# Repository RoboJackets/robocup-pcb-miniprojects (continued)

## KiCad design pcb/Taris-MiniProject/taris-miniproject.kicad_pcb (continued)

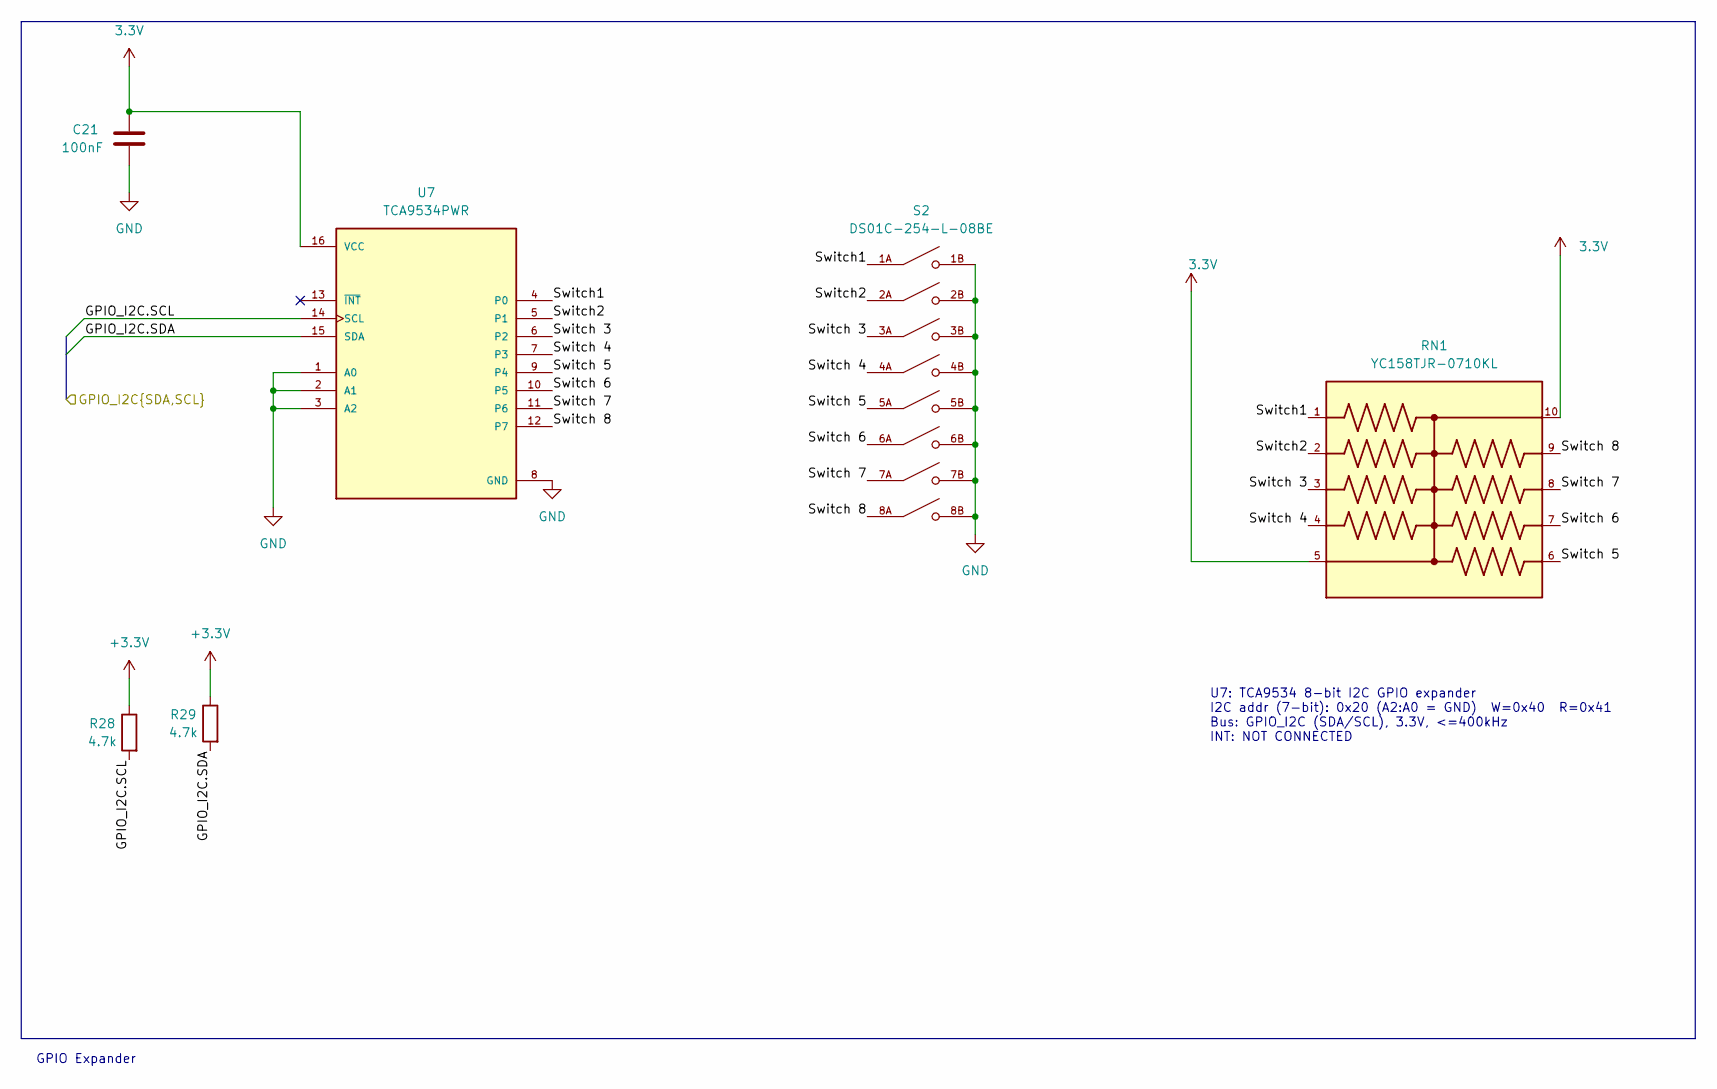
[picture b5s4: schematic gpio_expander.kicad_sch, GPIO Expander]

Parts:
C21: 100nF; C_0603_1608Metric; Manufacturer P/N CC0603KRX5R8BB104
R28, R29: 4.7k; R_0402_1005Metric; Manufacturer P/N RC0402FR-134K7L
RN1: YC158TJR-0710KL; RESCAXE64P320X160X70-10N; Manufacturer P/N YC158TJR-0710KL
S2: DS01C-254-L-08BE; SW_DS01C-254-L-08BE; PARTREV 1.0
U7: TCA9534PWR; SOP65P640X120-16N; PARTREV D

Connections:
3.3V: C21.1, RN1.5, RN1.10, U7.16 (VCC); also elsewhere on the board
+3.3V: R28.1, R29.1; also elsewhere on the board
/GPIO Expander/Switch1: RN1.1, S2.1A, U7.4 (P0)
/GPIO Expander/Switch2: RN1.2, S2.2A, U7.5 (P1)
/GPIO Expander/Switch 3: RN1.3, S2.3A, U7.6 (P2)
/GPIO Expander/Switch 4: RN1.4, S2.4A, U7.7 (P3)
/GPIO Expander/Switch 5: RN1.6, S2.5A, U7.9 (P4)
/GPIO Expander/Switch 6: RN1.7, S2.6A, U7.10 (P5)
/GPIO Expander/Switch 7: RN1.8, S2.7A, U7.11 (P6)
/GPIO Expander/Switch 8: RN1.9, S2.8A, U7.12 (P7)
/GPIO_I2C.SCL: R28.2, U7.14 (SCL); also elsewhere on the board
/GPIO_I2C.SDA: R29.2, U7.15 (SDA); also elsewhere on the board
GND: C21.2, S2.1B, S2.2B, S2.3B, S2.4B, S2.5B, S2.6B, S2.7B, S2.8B, U7.1 (A0), U7.2 (A1), U7.3 (A2), U7.8 (GND); also elsewhere on the board

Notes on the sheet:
U7: TCA9534 8-bit I2C GPIO expander I2C addr (7-bit): 0x20 (A2:A0 = GND) W=0x40 R=0x41 Bus: GPIO_I2C (SDA/SCL), 3.3V, <=400kHz INT: NOT CONNECTED
GPIO Expander

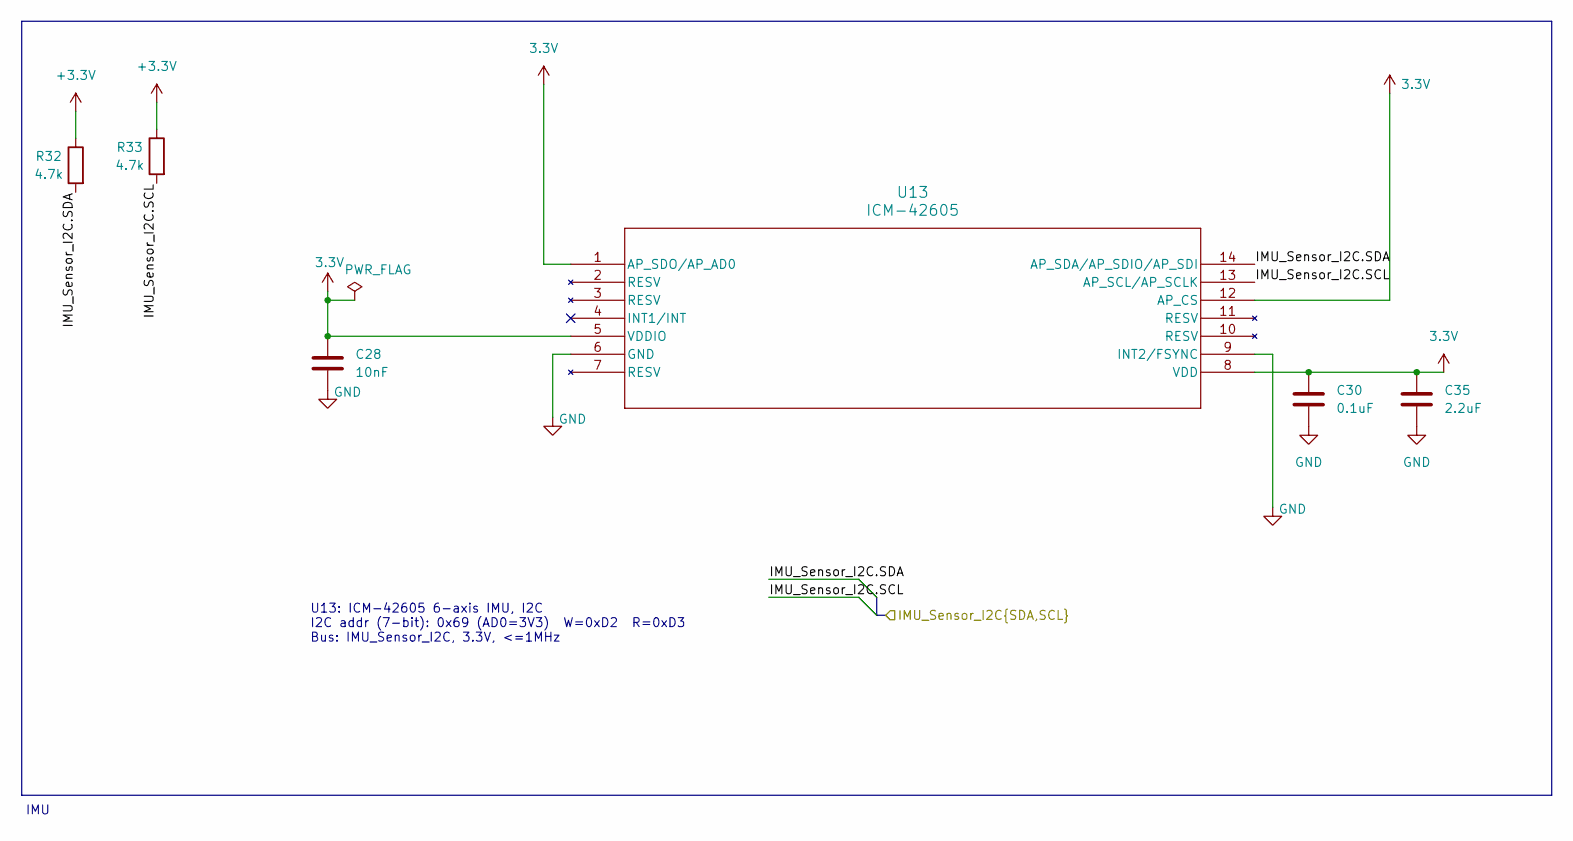
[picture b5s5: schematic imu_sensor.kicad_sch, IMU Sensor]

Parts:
C28: 10nF; C_0603_1608Metric; Manufacturer P/N GMC10X7R103K50NT
C30: 0.1uF; C_0603_1608Metric; Manufacturer P/N CC0603KRX5R8BB104
C35: 2.2uF; C_0603_1608Metric; Manufacturer P/N GMC10X7R225K25NT
R32, R33: 4.7k; R_0402_1005Metric; Manufacturer P/N RC0402FR-134K7L
U13: ICM-42605; LGA14_2P5X3X0P91_IVS; Manufacturer P/N ICM-42605

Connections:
3.3V: C28.1, C30.1, C35.1, U13.1 (AP_SDO/AP_AD0), U13.5 (VDDIO), U13.8 (VDD), U13.12 (AP_CS); also elsewhere on the board
+3.3V: R32.1, R33.1; also elsewhere on the board
/IMU_Sensor_I2C.SCL: R33.2, U13.13 (AP_SCL/AP_SCLK); also elsewhere on the board
/IMU_Sensor_I2C.SDA: R32.2, U13.14 (AP_SDA/AP_SDIO/AP_SDI); also elsewhere on the board
GND: C28.2, C30.2, C35.2, U13.6 (GND), U13.9 (INT2/FSYNC); also elsewhere on the board

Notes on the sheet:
IMU
U13: ICM-42605 6-axis IMU, I2C I2C addr (7-bit): 0x69 (AD0=3V3) W=0xD2 R=0xD3 Bus: IMU_Sensor_I2C, 3.3V, <=1MHz

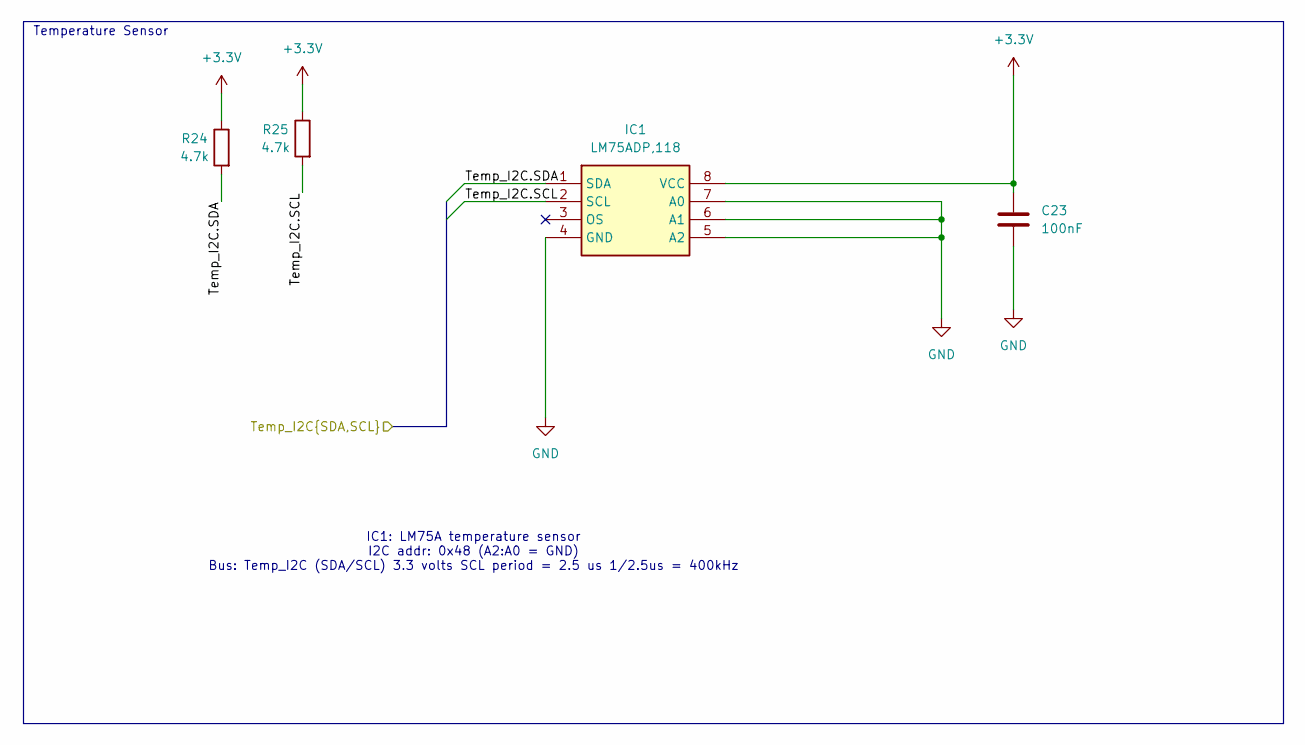
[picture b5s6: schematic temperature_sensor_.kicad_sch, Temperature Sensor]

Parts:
C23: 100nF; C_0603_1608Metric; Manufacturer P/N CC0603KRX5R8BB104
IC1: LM75ADP,118; SOP65P490X110-8N; Manufacturer_Part_Number LM75ADP,118; Mouser Part Number 771-LM75ADP-T
R24, R25: 4.7k; R_0402_1005Metric; Manufacturer P/N RC0402FR-134K7L

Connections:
+3.3V: C23.1, IC1.8 (VCC), R24.1, R25.1; also elsewhere on the board
/Temp_I2C.SCL: IC1.2 (SCL), R25.2; also elsewhere on the board
/Temp_I2C.SDA: IC1.1 (SDA), R24.2; also elsewhere on the board
GND: C23.2, IC1.4 (GND), IC1.5 (A2), IC1.6 (A1), IC1.7 (A0); also elsewhere on the board

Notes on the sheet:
IC1: LM75A temperature sensor I2C addr: 0x48 (A2:A0 = GND) Bus: Temp_I2C (SDA/SCL) 3.3 volts SCL period = 2.5 us 1/2.5us = 400kHz
Temperature Sensor

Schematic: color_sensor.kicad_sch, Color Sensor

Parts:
C27: 100nF; C_0603_1608Metric; Manufacturer P/N CC0603KRX5R8BB104
R30, R31: 4.7k; R_0402_1005Metric; Manufacturer P/N RC0402FR-134K7L
U12: VEML3328; Manufacturer P/N VEML3328

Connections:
3.3V: C27.1, U12.4 (VDD); also elsewhere on the board
+3.3V: R30.1, R31.1; also elsewhere on the board
/Color_I2C.SCL: R31.2, U12.3 (SCL); also elsewhere on the board
/Color_I2C.SDA: R30.2, U12.2 (SDA); also elsewhere on the board
GND: C27.2, U12.1 (GND); also elsewhere on the board

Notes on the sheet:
Color Sensor
U12: VEML3328 RGB/IR color sensor, I2C I2C addr (7-bit): 0x10 W=0x20 R=0x21 Bus: Color_I2C (SDA/SCL), 3.3V, <=400kHz

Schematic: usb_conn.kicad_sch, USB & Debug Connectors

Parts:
C17, C18, C24: 1u; C_0402_1005Metric; Manufacturer P/N GRM155Z71A105KE01J
J2: SWD; PinHeader_1x04_P2.54mm_Vertical; Manufacturer P/N 61300411121
J5: USB_B_Micro; USB_Micro-B_Amphenol_10118194-0001LF_Horizontal; Manufacturer P/N 10118194-0001LF
R13: 10K; R_0402_1005Metric; Manufacturer P/N RC0402FR-0710KL
U3: AP2112K-3.3; SOT-23-5; Manufacturer P/N AP2112K-3.3TRG1
U4, U5: USBLC6-2P6; SOT-666; Manufacturer P/N USBLC6-2SC6
U8, U9: LM66100DCK; SOT-363_SC-70-6; Manufacturer P/N LM66100DCKR

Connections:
+3.3V: C18.2, J2.1, U3.5 (VOUT), U5.5 (VBUS); also elsewhere on the board
/SLAVE_POWER: C17.2, C24.2, U3.1 (VIN), U3.3 (EN), U8.6 (VOUT), U9.6 (VOUT); also elsewhere on the board
/SPI_MASTER_INPUT: U8.3 (~CE), U9.1 (VIN); also elsewhere on the board
/SWD.CLK: U5.6 (I/O1); also elsewhere on the board
/SWD.DIO: U5.4 (I/O2); also elsewhere on the board
/USB.DM: U4.6 (I/O1); also elsewhere on the board
/USB.DP: U4.4 (I/O2); also elsewhere on the board
GND: C17.1, C18.1, C24.1, J2.4, J5.5 (GND), U3.2 (GND), U4.2 (GND), U5.2 (GND), U8.2 (GND), U9.2 (GND); also elsewhere on the board
unnamed: J2.2, U5.1 (I/O1)
unnamed: J2.3, U5.3 (I/O2)
unnamed: J5.3 (D+), U4.3 (I/O2)
unnamed: J5.2 (D-), U4.1 (I/O1)
unnamed: R13.1, U8.5 (ST), U9.3 (~CE)
VBUS: J5.1 (VBUS), R13.2, U4.5 (VBUS), U8.1 (VIN); also elsewhere on the board

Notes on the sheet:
SWD Debug Connector
Pull down resistor removed to avoid shorting the output. Capacitor kept so switching doesn't affect smoothness
Micro USB
MUX for SPI and Micro USB
3.3 V 600 mA LDO
0.5 mA of current when pulled low

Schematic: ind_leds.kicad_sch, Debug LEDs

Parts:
D3, D4, D5: RED; LED_0603_1608Metric; Manufacturer P/N LTST-C190KRKT
R15, R16, R17: 1k; R_0402_1005Metric; Manufacturer P/N RC0402FR-071KL

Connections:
3.3V: R17.2; also elsewhere on the board
/SLAVE_POWER: R16.2; also elsewhere on the board
GND: D3.1 (K), D4.1 (K), D5.1 (K); also elsewhere on the board
unnamed: D3.2 (A), R15.1
unnamed: D4.2 (A), R16.1
unnamed: D5.2 (A), R17.1
VBUS: R15.2; also elsewhere on the board

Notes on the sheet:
USB: 5 volts / 1 kOhm = 3.0 mA SPI_SLAVE_LED: 5 volts / 1 kOhm = 3.0 mA Color_Sensor_Power: 3.3 volts / 1 kOhm = 1.3 mA
Indicator LEDs

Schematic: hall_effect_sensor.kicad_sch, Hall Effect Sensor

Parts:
C22: 100nF; C_0603_1608Metric; Manufacturer P/N CC0603KRX5R8BB104
R26, R27: 4.7k; R_0402_1005Metric; Manufacturer P/N RC0402FR-134K7L
U11: TMAG5273C1QDBVR; SOT95P280X140-6N; PARTREV B

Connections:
3.3V: C22.1; also elsewhere on the board
+3.3V: R26.1, R27.1; also elsewhere on the board
/Hall_I2C.SCL: R26.2, U11.1 (SCL); also elsewhere on the board
/Hall_I2C.SDA: R27.2, U11.6 (SDA); also elsewhere on the board
GND: C22.2, U11.2 (GND), U11.3 (TEST), U11.4 (VCC); also elsewhere on the board

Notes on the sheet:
Hall Effect Sensor
U11: TMAG5273C1 3-axis Hall sensor, I2C I2C addr (7-bit): 0x78 (C1 default, VERIFY on HW) Bus: Hall_I2C (SDA/SCL), 3.3V, <=400kHz INT: NOT CONNECTED, set MASK_INTB=1 in firmware TEST: tied to GND (required)

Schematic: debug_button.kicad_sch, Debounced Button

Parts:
C15: 100nF; C_0402_1005Metric; Manufacturer P/N CC0603KRX5R8BB104
R7, R8: 10k; R_0402_1005Metric; Manufacturer P/N RC0402FR-0710KL
SW3: PTS810; SW_SPST_PTS810; Manufacturer P/N PTS810SJK250SMTR LFS

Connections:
+3.3V: SW3.1 (A); also elsewhere on the board
/MCU/gp_btn_a: C15.1, R8.2; also elsewhere on the board
GND: C15.2, R7.2; also elsewhere on the board
unnamed: R7.1, R8.1, SW3.2 (B)

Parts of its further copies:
C16: 100nF; C_0402_1005Metric; Manufacturer P/N CC0603KRX5R8BB104
R9, R10: 10k; R_0402_1005Metric; Manufacturer P/N RC0402FR-0710KL
SW4: PTS810; SW_SPST_PTS810; Manufacturer P/N PTS810SJK250SMTR LFS

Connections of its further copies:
+3.3V: SW4.1 (A); also elsewhere on the board
/MCU/gp_btn_b: C16.1, R10.2; also elsewhere on the board
GND: C16.2, R9.2; also elsewhere on the board
unnamed: R9.1, R10.1, SW4.2 (B)

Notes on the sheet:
RC low-pass filter -3 dB cutoff: 159.15 Hz

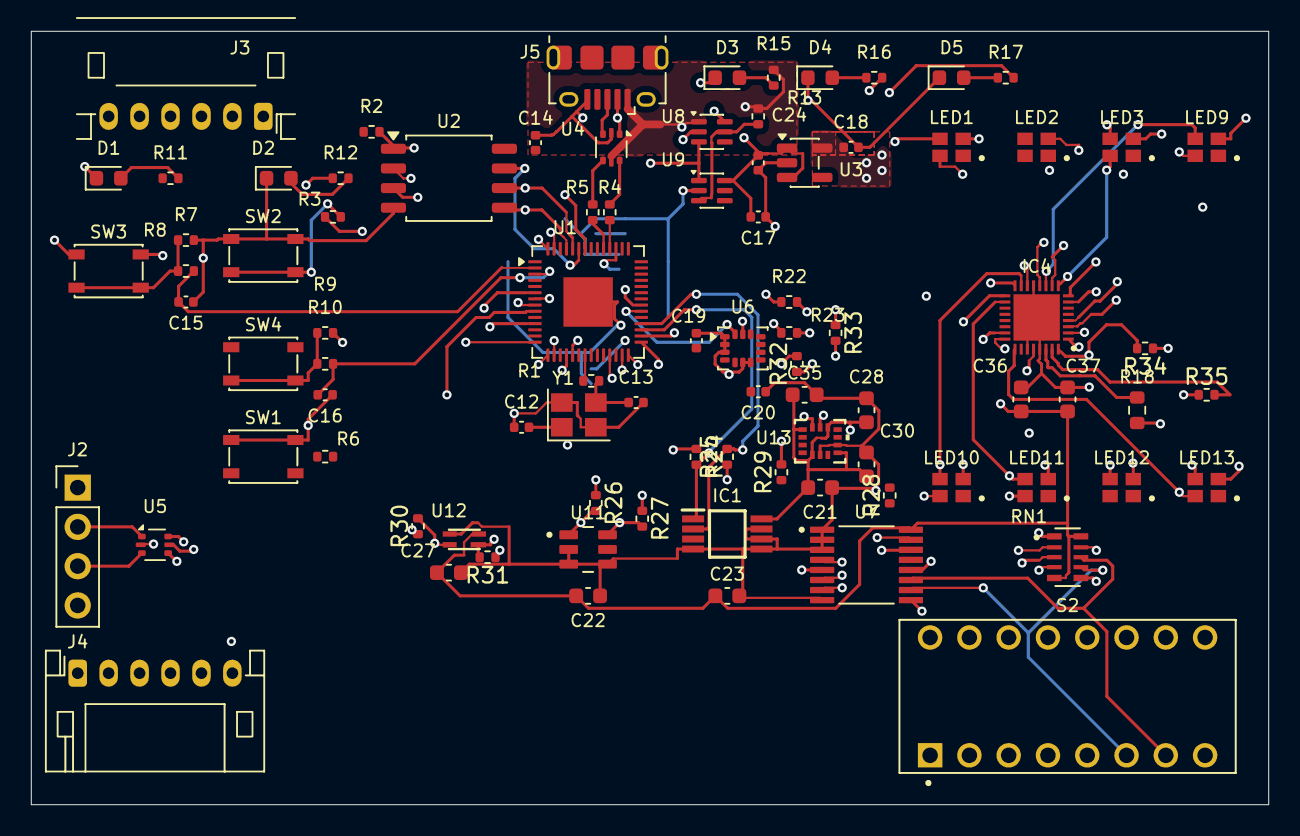
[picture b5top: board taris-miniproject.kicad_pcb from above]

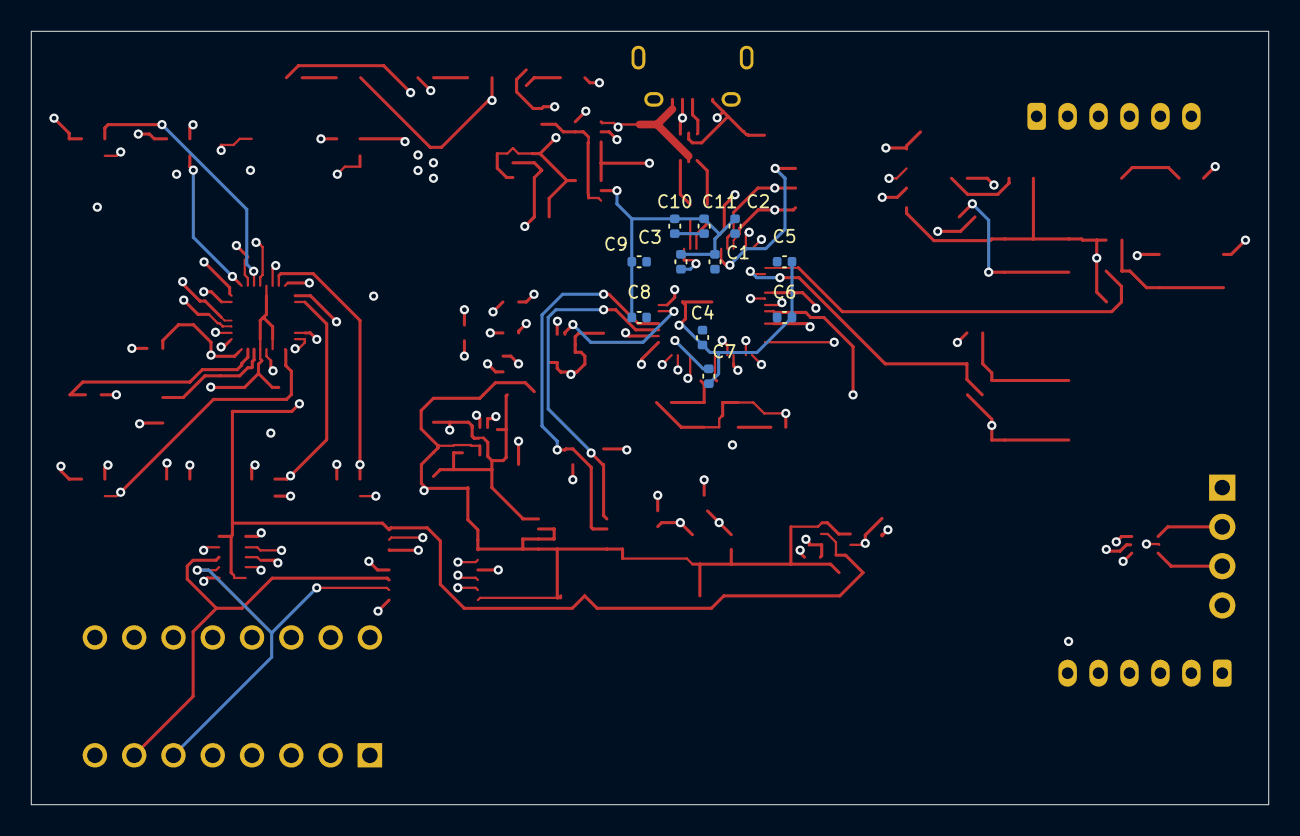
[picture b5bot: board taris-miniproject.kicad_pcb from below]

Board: 4 copper layers, 80.0 x 50.0 mm, 99 parts (11 on the bottom side), 95 nets.

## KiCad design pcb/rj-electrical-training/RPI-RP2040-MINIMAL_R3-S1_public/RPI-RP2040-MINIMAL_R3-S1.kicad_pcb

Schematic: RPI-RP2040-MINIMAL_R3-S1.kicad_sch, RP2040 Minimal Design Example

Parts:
C1, C4, C17: 10u; generic_capc2012x125; voltage 16V; tolerance 10%; part_uid RP-01GYSK-AVBE41
C2, C3: 15p; generic_capc1005x50; voltage 50V; tolerance 5%; part_uid RP-01C89W-LLY9XV
C5, C6, C7, C9, C11, C12, C13, C14, C15, C16: 100n; generic_capc1005x50; voltage 25V; tolerance 10%; part_uid RP-01BJ9Y-KRGF41
C8, C10: 1u; generic_capc1005x50; voltage 16V; tolerance 10%; part_uid RP-01GYSK-L7FEKV
J1: 10103594-0001LF; amphenol_10103594-0001lf; part_uid RP-019A1P-1JAX7V
J2: TSW-102-07-G-S; samtec_tsw-102-07-g-s; part_uid RP-01JV5X-LY21H5
J3, J4: TSW-118-07-L-D; samtec_tsw-118-07-l-d; part_uid RP-01JWH2-G371Y4
MH1, MH2, MH3, MH4: NPTH FD2.75mm SM3.15mm KO6mm; none_mh_npth_fd2p75mm_sm3p15mm_ko6mm; part_uid RP-01HF5R-LCTEJS
PCB1: R3; manufacturer_pn XXX
R1, R5: 1k; generic_resc1005x35; tolerance 1%; voltage 50V; part_uid RP-019A1P-4Z6ZWY
R2: 10k; generic_resc1005x35; tolerance 1%; voltage 50V; part_uid RP-019A1P-53DHSX; not fitted
R3, R4: 27; generic_resc1005x35; tolerance 1%; voltage 50V; part_uid RP-01C89V-LTEYC4
SBREV1: S1
U1: NCP1117ST33T3G; onsemi_ncp1117st33t3g; voltage 3.3V; part_uid RP-01JWD9-7JRX6J
U2: W25Q128JVSIQ; generic_soic127p790x195-8; voltage 2.7-3.6V; part_uid RP-01JWD4-F1H4N9
U3: RP2040; rpi_rp2040_vias; part_uid RP-01EKHS-ZTKTEH
VARIANT1: RPI-RP2040-MINIMAL
X1: 12MHz; generic_xtalcc320x250x80-4; tolerance 30ppm; part_uid RP-01G8X7-GS352B

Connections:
+1V1: C6.1, C7.1, C8.1, U3.23 (DVDD), U3.45 (VREG_VOUT), U3.50 (DVDD)
+3V3: C4.1, C5.1, C9.1, C10.1, C11.1, C12.1, C13.1, C14.1, C15.1, C16.1, C17.1, J3.2, R2.1, U1.2 (OUT), U1.4 (OUT), U2.8 (VCC), U3.1 (IOVDD), U3.10 (IOVDD), U3.22 (IOVDD), U3.33 (IOVDD), U3.42 (IOVDD), U3.43 (ADC_AVDD), U3.44 (VREG_IN), U3.48 (USB_VDD), U3.49 (IOVDD)
/GPIO0: J3.4, U3.2 (GPIO0)
/GPIO1: J3.6, U3.3 (GPIO1)
/GPIO2: J3.8, U3.4 (GPIO2)
/GPIO3: J3.10, U3.5 (GPIO3)
/GPIO4: J3.12, U3.6 (GPIO4)
/GPIO5: J3.14, U3.7 (GPIO5)
/GPIO6: J3.16, U3.8 (GPIO6)
/GPIO7: J3.18, U3.9 (GPIO7)
/GPIO8: J3.20, U3.11 (GPIO8)
/GPIO9: J3.22, U3.12 (GPIO9)
/GPIO10: J3.24, U3.13 (GPIO10)
/GPIO11: J3.26, U3.14 (GPIO11)
/GPIO12: J3.28, U3.15 (GPIO12)
/GPIO13: J3.30, U3.16 (GPIO13)
/GPIO14: J3.32, U3.17 (GPIO14)
/GPIO15: J3.34, U3.18 (GPIO15)
/GPIO16: J4.27, U3.27 (GPIO16)
/GPIO17: J4.25, U3.28 (GPIO17)
/GPIO18: J4.23, U3.29 (GPIO18)
/GPIO19: J4.21, U3.30 (GPIO19)
/GPIO20: J4.19, U3.31 (GPIO20)
/GPIO21: J4.17, U3.32 (GPIO21)
/GPIO22: J4.15, U3.34 (GPIO22)
/GPIO23: J4.13, U3.35 (GPIO23)
/GPIO24: J4.11, U3.36 (GPIO24)
/GPIO25: J4.9, U3.37 (GPIO25)
/GPIO26_ADC0: J4.7, U3.38 (GPIO26_ADC0)
/GPIO27_ADC1: J4.5, U3.39 (GPIO27_ADC1)
/GPIO28_ADC2: J4.3, U3.40 (GPIO28_ADC2)
/GPIO29_ADC3: J4.1, U3.41 (GPIO29_ADC3)
/QSPI_SCLK: U2.6 (CLK), U3.52 (QSPI_SCLK)
/QSPI_SD0: U2.5 (DI_IO0), U3.53 (QSPI_SD0)
/QSPI_SD1: U2.2 (DO_IO1), U3.55 (QSPI_SD1)
/QSPI_SD2: U2.3 (~WP_IO2), U3.54 (QSPI_SD2)
/QSPI_SD3: U2.7 (~HOLD_IO3), U3.51 (QSPI_SD3)
/QSPI_SS: R1.1, R2.2, U2.1 (~CS), U3.56 (QSPI_~SS)
/RUN: J4.29, U3.26 (RUN)
/SWCLK: J4.33, U3.24 (SWCLK)
/SWD: J4.31, U3.25 (SWD)
/USB_D+: J1.3 (D+), R3.1
/USB_D-: J1.2 (D-), R4.1
/XIN: C2.1, U3.20 (XIN), X1.1
/XOUT: R5.2, U3.21 (XOUT)
/~USB_BOOT: J2.1, R1.2
GND: C1.2, C2.2, C3.2, C4.2, C5.2, C6.2, C7.2, C8.2, C9.2, C10.2, C11.2, C12.2, C13.2, C14.2, C15.2, C16.2, C17.2, J1.5 (GND), J1.6 (SH), J1.7 (SH), J1.8 (SH), J1.9 (SH), J1.10 (SH), J1.11 (SH), J2.2, J3.1, J3.3, J3.5, J3.7, J3.9, J3.11, J3.13, J3.15, J3.17, J3.19, J3.21, J3.23, J3.25, J3.27, J3.29, J3.31, J3.33, J3.35, J3.36, J4.2, J4.4, J4.6, J4.8, J4.10, J4.12, J4.14, J4.16, J4.18, J4.20, J4.22, J4.24, J4.26, J4.28, J4.30, J4.32, J4.34, J4.35, J4.36, U1.1 (GND), U2.4 (GND), U3.19 (TESTEN), U3.57 (GND), X1.2, X1.4
unnamed: C3.1, R5.1, X1.3
unnamed: R4.2, U3.46 (USB_DM)
unnamed: R3.2, U3.47 (USB_DP)
VBUS: C1.1, J1.1 (VCC), U1.3 (IN)

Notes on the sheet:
IOs
Power
Crystal
Make sure C8 is close to pin 45 of RP2040
Make sure C10 is close to pin 44 of RP2040
Note: S1 schematic revision indicates that this is the 1st revision of the schematic/BOM associated with the R3 PCB. R3-S1 therefore uniquely identifies the fully built PCB Assembly (PCBA). This is a change from the previous revision numbering to align with the internal Raspberry Pi product revisio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
Make sure R3 and R4 are close to RP2040
Flash

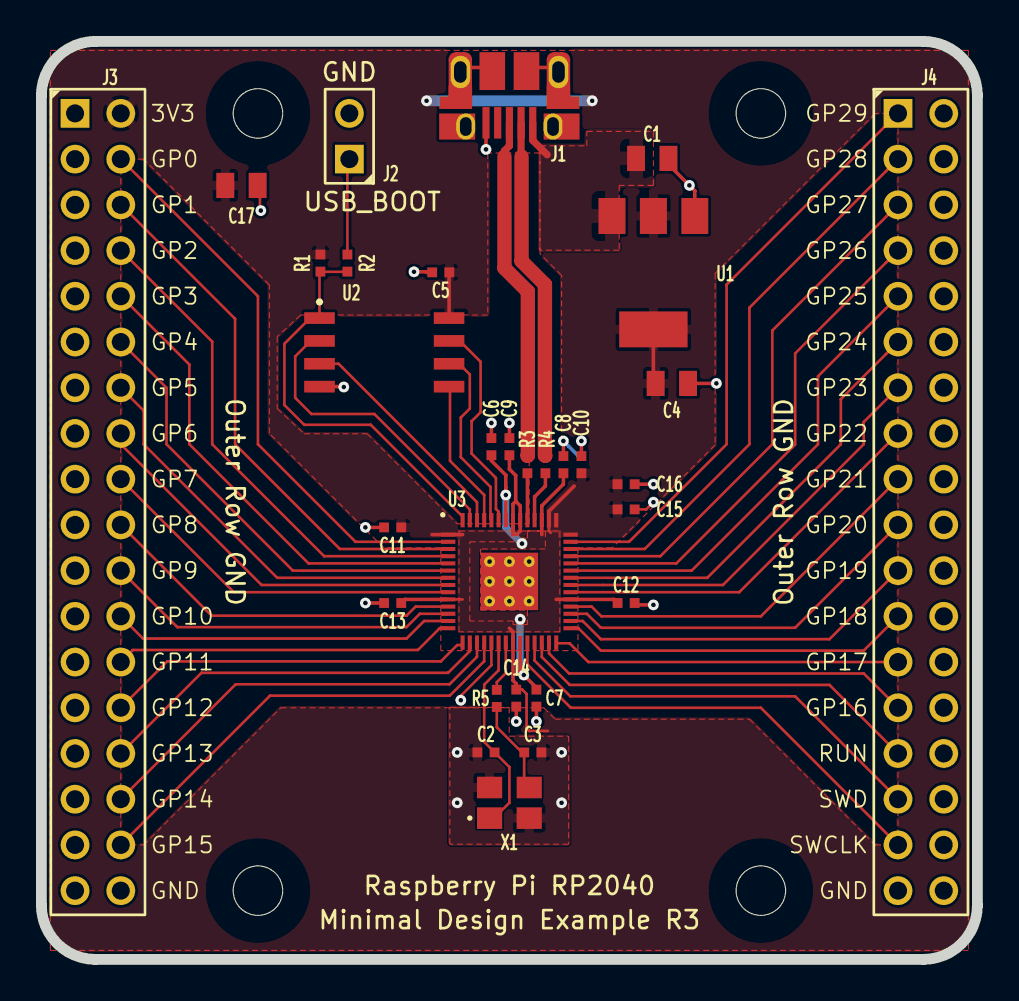
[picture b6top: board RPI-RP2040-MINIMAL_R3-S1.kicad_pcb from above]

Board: 2 copper layers, 52.0 x 51.0 mm, 34 parts (0 on the bottom side), 51 nets.

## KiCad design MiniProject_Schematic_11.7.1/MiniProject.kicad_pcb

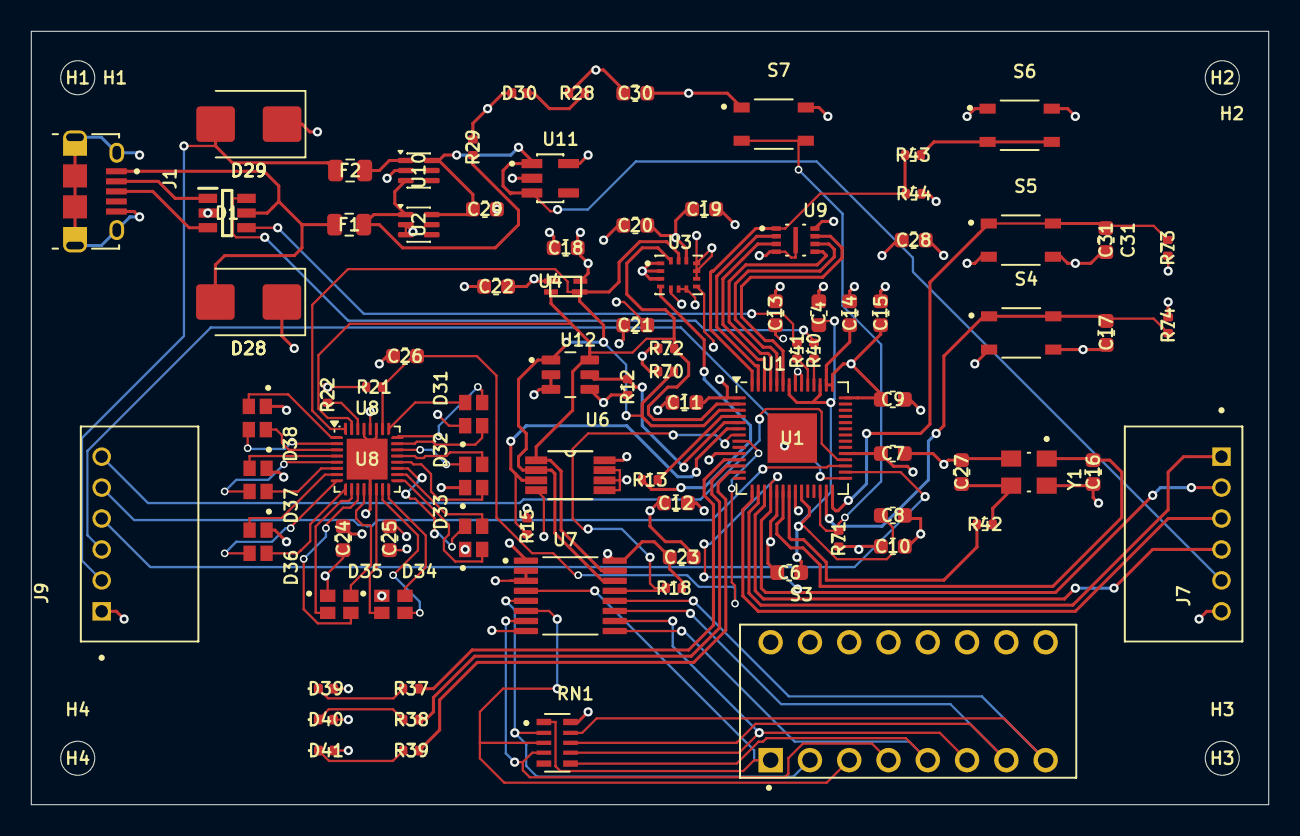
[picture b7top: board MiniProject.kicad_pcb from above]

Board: 4 copper layers, 80.0 x 50.0 mm, 90 parts (0 on the bottom side), 83 nets.

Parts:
C4, C6, C7, C9, C11, C12, C13, C14, C15, C17, C28, C31: 100n; C_0603_1608Metric
C8, C10: 1u; C_0603_1608Metric
C16, C27: 15p; C_0603_1608Metric
C18, C22, C23, C25, C26: 0.1uf; C_0603_1608Metric
C19, C20, C21: C_Small; C_0603_1608Metric
C24, C29, C30: 1uf; C_0603_1608Metric
D1: USBLC6-2SC6Y; SOT95P280X145-6N
D28, D29: SMBJ5.0CA; D_SMB
D30, D39, D40, D41: LED; LED_0402_1005Metric
D31, D32, D33, D34, D35, D36, D37, D38: CLMVC-FKA-CL1D1L71BB7C3C3; LED_CLMVC-FKA-CL1D1L71BB7C3C3
F1, F2: 750m; Fuse_0805_2012Metric
H1, H2, H3, H4: MountingHole_2.2mm_M2
J1: 10118194-0001LF; AMPHENOL_10118194-0001LF
J7, J9: S6B-PH-K-S_LF__SN_; JST_S6B-PH-K-S_LF__SN_
R12, R13, R70, R72: 4.7k; R_0402_1005Metric
R15, R18, R44, R73, R74: 10k; R_0402_1005Metric
R21, R29: 100k; R_0402_1005Metric
R22: 3.3k; R_0402_1005Metric
R28, R37, R38, R39, R42, R43, R71: 1k; R_0402_1005Metric
R40, R41: 27; R_0402_1005Metric
RN1: YC158TJR-0710KL; RESCAXE64P320X160X70-10N
S3: DS01C-254-L-08BE; SW_DS01C-254-L-08BE
S4, S5, S6, S7: SKRPABE010; SW_SKRPABE010
U1: RP2040; QFN-56-1EP_7x7mm_P0.4mm_EP3.2x3.2mm
U2, U10: LM66100DCK; SOT-363_SC-70-6
U3: ICM-42605; XDCR_ICM-42605
U4: VEML3328
U6: LM75ADP; SOP65P490X110-8N
U7: TCA9534PWR; SOP65P640X120-16N
U8: IS31FL3254-QFLS4-TR; QFN-32-1EP_4x4mm_P0.4mm_EP2.65x2.65mm
U9: W25Q16JVUXIQ_TR; IC_W25Q16JVUXIQ_TR
U11: AP2112K-3.3TRG1; SOT95P285X140-5N
U12: TMAG5273A2QDBVR; SOT95P280X140-6N
Y1: ABM8-272-T3; XTAL_ABM8-272-T3

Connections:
+1V1: C4.1, C6.1, C8.1, U1.23 (DVDD), U1.45 (VREG_VOUT), U1.50 (DVDD)
+3V3: C7.1, C9.1, C10.1, C11.1, C12.1, C13.1, C14.1, C15.1, C18.1, C19.1, C20.1, C21.1, C22.1, C23.1, C24.1, C25.1, C28.1, C30.1, D31.1, D32.1, D33.1, D34.1, D35.1, D36.1, D37.1, D38.1, D39.2 (A), D40.2 (A), D41.2 (A), R12.1, R15.2, R18.1, R28.1, R44.1, R70.1, R71.1, R72.1, R73.1, R74.1, RN1.10, U1.1 (IOVDD), U1.10 (IOVDD), U1.22 (IOVDD), U1.33 (IOVDD), U1.42 (IOVDD), U1.43 (ADC_AVDD), U1.44 (VREG_VIN), U1.48 (USB_VDD), U1.49 (IOVDD), U3.5 (VDDIO), U3.8 (VDD), U3.12 (AP_CS), U4.4 (VDD), U6.8 (VCC), U7.1 (A0), U7.16 (VCC), U8.28 (VCC), U9.8 (VCC), U11.5 (VOUT), U12.4 (VCC)
/LEDs and Driver/OUT1_R1: D38.4, U8.1 (OUT1_R1)
/LEDs and Driver/OUT2_G1: D38.3, U8.2 (OUT2_G1)
/LEDs and Driver/OUT3_B1: D38.2, U8.3 (OUT3_B1)
/LEDs and Driver/OUT4_R2: D37.4, U8.4 (OUT4_R2)
/LEDs and Driver/OUT5_G2: D37.3, U8.5 (OUT5_G2)
/LEDs and Driver/OUT6_B2: D37.2, U8.6 (OUT6_B2)
/LEDs and Driver/OUT7_R3: D36.4, U8.7 (OUT7_R3)
/LEDs and Driver/OUT8_G3: D36.3, U8.8 (OUT8_G3)
/LEDs and Driver/OUT9_B3: D36.2, U8.9 (OUT9_B3)
/LEDs and Driver/OUT10_R4: D35.4, U8.10 (OUT10_R4)
/LEDs and Driver/OUT11_G4: D35.3, U8.11 (OUT11_G4)
/LEDs and Driver/OUT12_B4: D35.2, U8.12 (OUT12_B4)
/LEDs and Driver/OUT13_R5: D34.4, U8.14 (OUT13_R5)
/LEDs and Driver/OUT14_G5: D34.3, U8.15 (OUT14_G5)
/LEDs and Driver/OUT15_B5: D34.2, U8.16 (OUT15_B5)
/LEDs and Driver/OUT16_R6: D33.4, U8.17 (OUT16_R6)
/LEDs and Driver/OUT17_G6: D33.3, U8.18 (OUT17_G6)
/LEDs and Driver/OUT18_B6: D33.2, U8.19 (OUT18_B6)
/LEDs and Driver/OUT19_R7: D32.4, U8.20 (OUT19_R7)
/LEDs and Driver/OUT20_G7: D32.3, U8.21 (OUT20_G7)
/LEDs and Driver/OUT21_B7: D32.2, U8.22 (OUT21_B7)
/LEDs and Driver/OUT22_R8: D31.4, U8.23 (OUT22_R8)
/LEDs and Driver/OUT23_G8: D31.3, U8.24 (OUT23_G8)
/LEDs and Driver/OUT24_B8: D31.2, U8.25 (OUT24_B8)
/LEDs and Driver/SCL: R70.2, U1.3 (GPIO1), U3.13 (AP_SCL/AP_SCLK), U4.3 (SCL), U6.2 (SCL), U7.14 (SCL), U8.32 (SCL), U12.1 (SCL)
/LEDs and Driver/SDA: R72.2, U1.2 (GPIO0), U3.14 (AP_SDA/AP_SDIO/AP_SDI), U4.2 (SDA), U6.1 (SDA), U7.15 (SDA), U8.31 (SDA), U12.6 (SDA)
/LEDs and Driver/SDB_LEDDriver: C26.1, R21.2, U1.8 (GPIO6), U8.26 (SDB)
/MCU Sheet/GPIO16: C17.1, R74.2, S4.1, S4.2, U1.27 (GPIO16)
/MCU Sheet/GPIO17: C31.1, R73.2, S5.1, S5.2, U1.28 (GPIO17)
/MCU Sheet/INT_GPIOExpander: R18.2, U1.7 (GPIO5), U7.13 (~INT)
/MCU Sheet/INT_HallEffect: R12.2, U1.5 (GPIO3), U12.5 (~INT)
/MCU Sheet/INT_IMU: R13.2, U1.4 (GPIO2)
/MCU Sheet/INT_Temperature: R15.1, U1.6 (GPIO4), U6.3 (OS)
/MCU Sheet/QSPI_SCLK: U1.52 (QSPI_SCLK), U9.6 (CLK)
/MCU Sheet/QSPI_SD0: U1.53 (QSPI_SD0), U9.5 (DI/IO0)
/MCU Sheet/QSPI_SD1: U1.55 (QSPI_SD1), U9.2 (DO/IO1)
/MCU Sheet/QSPI_SD2: U1.54 (QSPI_SD2), U9.3 (~WP/IO2)
/MCU Sheet/QSPI_SD3: U1.51 (QSPI_SD3), U9.7 (~HOLD/~RESET/IO3)
/MCU Sheet/QSPI_SS: R43.1, R44.2, U1.56 (~QSPI_SS)
/MCU Sheet/SPI_5V_IN: D29.2 (A2), F2.1, J9.2
/MCU Sheet/SPI_5V_OUT: C29.1, J7.5, U2.6 (VOUT), U10.6 (VOUT), U11.1 (VIN), U11.3 (EN)
/MCU Sheet/SPI_IN_CSN: J9.6, U1.32 (GPIO21)
/MCU Sheet/SPI_IN_MISO: J9.4, U1.30 (GPIO19)
/MCU Sheet/SPI_IN_MOSI: J9.5, U1.31 (GPIO20)
/MCU Sheet/SPI_IN_SCK: J9.3, U1.29 (GPIO18)
/MCU Sheet/SPI_OUT_CSN: J7.1, U1.16 (GPIO13)
/MCU Sheet/SPI_OUT_MISO: J7.3, U1.15 (GPIO12)
/MCU Sheet/SPI_OUT_MOSI: J7.2, U1.18 (GPIO15)
/MCU Sheet/SPI_OUT_SCK: J7.4, U1.17 (GPIO14)
/MCU Sheet/USB_D+: D1.4 (I/O2_2), R41.2
/MCU Sheet/USB_D-: D1.6 (I/O1_2), R40.2
/MCU Sheet/XIN: C16.2, U1.20 (XIN), Y1.1
/MCU Sheet/XOUT: R42.1, U1.21 (XOUT)
/MCU Sheet/~USB_BOOT: R43.2, S6.3, S6.4
/Sensors Sheet/SW0: RN1.1, S3.1A, U7.4 (P0)
/Sensors Sheet/SW1: RN1.2, S3.2A, U7.5 (P1)
/Sensors Sheet/SW2: RN1.3, S3.3A, U7.6 (P2)
/Sensors Sheet/SW3: RN1.4, S3.4A, U7.7 (P3)
/Sensors Sheet/SW4: RN1.6, S3.5A, U7.9 (P4)
/Sensors Sheet/SW5: RN1.7, S3.6A, U7.10 (P5)
/Sensors Sheet/SW6: RN1.8, S3.7A, U7.11 (P6)
/Sensors Sheet/SW7: RN1.9, S3.8A, U7.12 (P7)
GND: C4.2, C6.2, C7.2, C8.2, C9.2, C10.2, C11.2, C12.2, C13.2, C14.2, C15.2, C16.1, C17.2, C18.2, C19.2, C20.2, C21.2, C22.2, C23.2, C24.2, C25.2, C26.2, C27.1, C28.2, C29.2, C30.2, C31.2, D1.2 (GND), D28.1 (A1), D29.1 (A1), D30.1 (K), J1.5 (GND), J1.SH1 (SHIELD), J1.SH2 (SHIELD), J1.SH3 (SHIELD), J1.SH4 (SHIELD), J1.SH5 (SHIELD), J1.SH6 (SHIELD), J7.6, J9.1, R21.1, R22.1, R29.1, S3.1B, S3.2B, S3.3B, S3.4B, S3.5B, S3.6B, S3.7B, S3.8B, S4.3, S4.4, S5.3, S5.4, S6.1, S6.2, S7.1, S7.2, U1.19 (TESTEN), U1.57 (GND), U2.2 (GND), U2.3 (~CE), U3.1 (AP_SDO/AP_AD0), U3.2 (RESV), U3.3 (RESV), U3.6 (GND), U3.7 (RESV), U3.9 (INT2/FSYNC), U3.10 (RESV), U3.11 (RESV), U4.1 (GND), U6.4 (GND), U6.5 (A2), U6.6 (A1), U6.7 (A0), U7.2 (A1), U7.3 (A2), U7.8 (GND), U8.13 (GND), U8.27 (AD), U8.29 (GND), U8.33 (EP), U9.4 (GND), U9.9 (EXP), U10.2 (GND), U11.2 (GND), U12.2 (GND), U12.3 (TEST), Y1.2 (GND), Y1.4 (GND)
unnamed: C27.2, R42.2, Y1.3
unnamed: D1.1 (I/O1_1), J1.2 (D-)
unnamed: D1.3 (I/O2_1), J1.3 (D+)
unnamed: D1.5 (VBUS), D28.2 (A2), F1.1, J1.1 (VCC)
unnamed: D30.2 (A), R28.2
unnamed: D39.1 (K), R37.1
unnamed: D40.1 (K), R38.1
unnamed: D41.1 (K), R39.1
unnamed: R37.2, U1.11 (GPIO8)
unnamed: R38.2, U1.12 (GPIO9)
unnamed: R39.2, U1.13 (GPIO10)
unnamed: R71.2, S7.3, S7.4, U1.26 (RUN)
unnamed: R40.1, U1.46 (USB_DM)
unnamed: R41.1, U1.47 (USB_DP)
unnamed: R13.1, U3.4 (INT1/INT)
unnamed: R22.2, U8.30 (ISET)
unnamed: F2.2, U10.1 (VIN)
unnamed: F1.2, R29.2, U2.1 (VIN), U10.3 (~CE)

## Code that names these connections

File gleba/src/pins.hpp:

#pragma once
// GPIO assignments, schematic Rev 11.7.1
// Owner: shared (agree before changing)

// ---- I2C: one bus per device (only 2 controllers -> switch with gpio_set_function) ----
#define PIN_SDA_IMU      0   // I2C0
#define PIN_SCL_IMU      1   // I2C0
#define PIN_SDA_TEMP     2   // I2C1
#define PIN_SCL_TEMP     3   // I2C1
#define PIN_SDA_HALL     4   // I2C0
#define PIN_SCL_HALL     5   // I2C0
#define PIN_SDA_GPIO     22  // I2C1 (GPIO expander)
#define PIN_SCL_GPIO     23  // I2C1
#define PIN_SDA_COLOR    24  // I2C0
#define PIN_SCL_COLOR    25  // I2C0
#define PIN_SDA_LED      26  // I2C1 (LED driver)
#define PIN_SCL_LED      27  // I2C1

#define I2C_BAUD_HZ      (400 * 1000)

#define PIN_LED_SDB      6   // IS31FL3254 enable, high = on (100k pull-down)

// ---- Debug LEDs (active-low: write 0 to turn on) ----
#define PIN_LED_D39      8
#define PIN_LED_D40      9
#define PIN_LED_D41      10

// ---- Buttons (active-low: read 0 when pressed, RC debounced) ----
#define PIN_BUTTON_1     16  // S4
#define PIN_BUTTON_2     17  // S5

// ---- SPI OUT: SPI1, we are MASTER (to next board, J7) ----
#define PIN_SPI_OUT_MISO 12  // SPI1 RX  (we receive)
#define PIN_SPI_OUT_CSN  13  // SPI1 CSn
#define PIN_SPI_OUT_SCK  14  // SPI1 SCK
#define PIN_SPI_OUT_MOSI 15  // SPI1 TX  (we send)

// ---- SPI IN: SPI0, we are SLAVE (from previous board, J9) ----
#define PIN_SPI_IN_SCK   18  // SPI0 SCK
#define PIN_SPI_IN_MISO  19  // SPI0 TX  (we send back to master)
#define PIN_SPI_IN_MOSI  20  // SPI0 RX  (we receive)
#define PIN_SPI_IN_CSN   21  // SPI0 CSn

#define SPI_BAUD_HZ      (1000 * 1000)   // 1 MHz, mode 3 (CPOL = 1, CPHA = 1)

// Unused: GPIO 7, 11, 28, 29
